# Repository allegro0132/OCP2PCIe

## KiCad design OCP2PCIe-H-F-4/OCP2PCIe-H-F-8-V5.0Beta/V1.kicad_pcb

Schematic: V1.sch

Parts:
C1: C; CP_Elec_6.3x5.4
C2: C; CP_EIA-7343-31_Kemet-D
C3, C4: C; C_1206_3216Metric
J1: PCIe_x8; BUS_PCIexpress_x8
J2: Conn_02x40_Top_Bottom; OCP_Mezz_V2.0
J3, J4: Conn_01x02; PinHeader_1x02_P2.54mm_Vertical
TP1: TestPoint_2Pole; TestPlot
U1: DM02

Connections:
3V3AUX: J1.B10, J2.7, J2.66
+3V3: J1.A9, J1.A10, J1.B8, J2.10, J2.11, J2.12, J2.13, J2.69, J2.70, J2.71, J2.72
+12V: C1.1, J1.A2, J1.A3, J1.B1, J1.B2, J1.B3, J2.61, J2.62, J2.63, J3.1, TP1.1, U1.4
GND: C1.2, C2.2, C3.2, C4.2, J1.A4, J1.A12, J1.A15, J1.A18, J1.A20, J1.A23, J1.A24, J1.A27, J1.A28, J1.A31, J1.A34, J1.A37, J1.A38, J1.A41, J1.A42, J1.A45, J1.A46, J1.A49, J1.B4, J1.B7, J1.B13, J1.B16, J1.B18, J1.B21, J1.B22, J1.B25, J1.B26, J1.B29, J1.B32, J1.B35, J1.B36, J1.B39, J1.B40, J1.B43, J1.B44, J1.B47, J1.B49, J2.5, J2.6, J2.8, J2.9, J2.20, J2.21, J2.24, J2.25, J2.28, J2.29, J2.32, J2.33, J2.36, J2.37, J2.40, J2.41, J2.44, J2.45, J2.48, J2.49, J2.52, J2.53, J2.56, J2.57, J2.60, J2.64, J2.65, J2.67, J2.68, J2.73, J2.79, J2.82, J2.83, J2.86, J2.87, J2.90, J2.91, J2.94, J2.95, J2.98, J2.99, J2.102, J2.103, J2.106, J2.107, J2.110, J2.111, J2.114, J2.115, J2.118, J2.119, J3.2, J4.2, U1.2, U1.3
HSI0_N: J1.A17, J2.31
HSI0_P: J1.A16, J2.30
HSI1_N: J1.A22, J2.35
HSI1_P: J1.A21, J2.34
HSI2_N: J1.A26, J2.39
HSI2_P: J1.A25, J2.38
HSI3_N: J1.A30, J2.43
HSI3_P: J1.A29, J2.42
HSI4_N: J1.A36, J2.47
HSI4_P: J1.A35, J2.46
HSI5_N: J1.A40, J2.51
HSI5_P: J1.A39, J2.50
HSI6_N: J1.A44, J2.55
HSI6_P: J1.A43, J2.54
HSI7_N: J1.A48, J2.59
HSI7_P: J1.A47, J2.58
HSO0_N: J1.B15, J2.89
HSO0_P: J1.B14, J2.88
HSO1_N: J1.B20, J2.93
HSO1_P: J1.B19, J2.92
HSO2_N: J1.B24, J2.97
HSO2_P: J1.B23, J2.96
HSO3_N: J1.B28, J2.101
HSO3_P: J1.B27, J2.100
HSO4_N: J1.B34, J2.105
HSO4_P: J1.B33, J2.104
HSO5_N: J1.B38, J2.109
HSO5_P: J1.B37, J2.108
HSO6_N: J1.B42, J2.113
HSO6_P: J1.B41, J2.112
HSO7_N: J1.B46, J2.117
HSO7_P: J1.B45, J2.116
P5V_AUX: C2.1, C3.1, C4.1, J2.2, J2.3, J2.4, J4.1, TP1.2, U1.1
PERST: J1.A11, J2.17
PRSNT1: J1.A1, J2.1
PRSNT2: J1.B48, J2.120
REFCLK+: J1.A13, J2.26, J2.84
REFCLK-: J1.A14, J2.27, J2.85
WAKE: J1.B11, J2.77

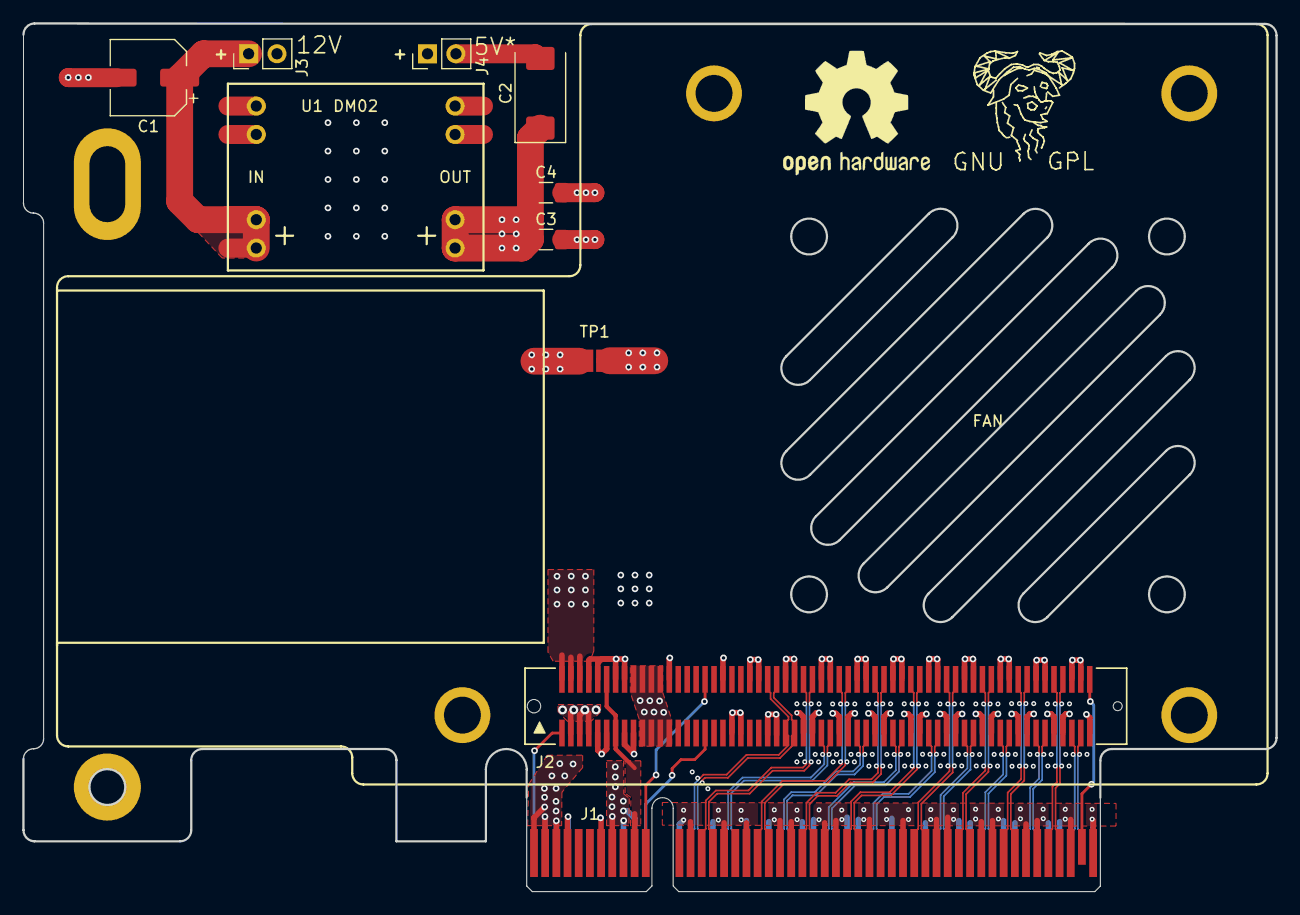
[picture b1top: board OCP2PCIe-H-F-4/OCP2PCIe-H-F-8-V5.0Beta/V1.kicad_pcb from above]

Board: 4 copper layers, 112.1 x 77.6 mm, 11 parts (0 on the bottom side), 43 nets.

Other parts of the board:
FAN: Fan_4010

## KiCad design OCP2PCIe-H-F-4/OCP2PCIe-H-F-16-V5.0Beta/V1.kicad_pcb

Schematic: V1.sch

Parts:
C1, C2, C4, C5: 1uf; C_0402_1005Metric_Pad0.74x0.62mm_HandSolder
C3, C6: 10uf; C_0603_1608Metric_Pad1.08x0.95mm_HandSolder
C7: C; CP_Elec_6.3x5.4
C8: C; CP_EIA-7343-31_Kemet-D
C9, C10: C; C_1206_3216Metric
J1: PCIe_x16; BUS_PCIexpress_x16
J2, J3: Conn_02x40_Top_Bottom; OCP_Mezz_V2.0
J4, J5: Conn_01x02; PinHeader_1x02_P2.54mm_Vertical
L1, L2: L; L_0603_1608Metric_Pad1.05x0.95mm_HandSolder
R2, R6: 34.46; R_0402_1005Metric_Pad0.72x0.64mm_HandSolder
R3, R4, R5, R7, R8, R9: R; R_0402_1005Metric_Pad0.72x0.64mm_HandSolder
TP1: TestPoint_2Pole; TestPlot
U1: DM02
U2: 9DBL411B; SOP65P640X120-20N

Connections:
3V3AUX: J1.B10, J2.7, J2.66, J3.7, J3.66
3V3_A: C1.1, C2.1, C3.1, L1.1, U2.4
3V3_D: C4.1, C5.1, C6.1, L2.1, U2.9, U2.18
+3V3: J1.A9, J1.A10, J1.B8, J2.10, J2.11, J2.12, J2.13, J2.69, J2.70, J2.71, J2.72, J3.10, J3.11, J3.12, J3.13, J3.69, J3.70, J3.71, J3.72, L1.2, L2.2
+12V: C7.1, J1.A2, J1.A3, J1.B1, J1.B2, J1.B3, J2.61, J2.62, J2.63, J3.61, J3.62, J3.63, J4.1, TP1.1, U1.4
DIF0_N: R2.2, U2.20
DIF0_P: R3.2, U2.19
DIF1_N: R4.2, U2.15
DIF1_P: R5.2, U2.14
DIF2_N: R6.2, U2.8
DIF2_P: R7.2, U2.7
DIF3_N: R8.2, U2.12
DIF3_P: R9.2, U2.11
GND: C1.2, C2.2, C3.2, C4.2, C5.2, C6.2, C7.2, C8.2, C9.2, C10.2, J1.A4, J1.A12, J1.A15, J1.A18, J1.A20, J1.A23, J1.A24, J1.A27, J1.A28, J1.A31, J1.A34, J1.A37, J1.A38, J1.A41, J1.A42, J1.A45, J1.A46, J1.A49, J1.A50, J1.A51, J1.A54, J1.A55, J1.A58, J1.A59, J1.A62, J1.A63, J1.A66, J1.A67, J1.A70, J1.A71, J1.A74, J1.A75, J1.A78, J1.A79, J1.A82, J1.B4, J1.B7, J1.B13, J1.B16, J1.B18, J1.B21, J1.B22, J1.B25, J1.B26, J1.B29, J1.B32, J1.B35, J1.B36, J1.B39, J1.B40, J1.B43, J1.B44, J1.B47, J1.B49, J1.B52, J1.B53, J1.B56, J1.B57, J1.B60, J1.B61, J1.B64, J1.B65, J1.B68, J1.B69, J1.B72, J1.B73, J1.B76, J1.B77, J1.B80, J1.B82, J2.5, J2.6, J2.8, J2.9, J2.20, J2.21, J2.24, J2.25, J2.28, J2.29, J2.32, J2.33, J2.36, J2.37, J2.40, J2.41, J2.44, J2.45, J2.48, J2.49, J2.52, J2.53, J2.56, J2.57, J2.60, J2.64, J2.65, J2.67, J2.68, J2.73, J2.79, J2.82, J2.83, J2.86, J2.87, J2.90, J2.91, J2.94, J2.95, J2.98, J2.99, J2.102, J2.103, J2.106, J2.107, J2.110, J2.111, J2.114, J2.115, J2.118, J2.119, J3.5, J3.6, J3.8, J3.9, J3.20, J3.21, J3.24, J3.25, J3.28, J3.29, J3.32, J3.33, J3.36, J3.37, J3.40, J3.41, J3.44, J3.45, J3.48, J3.49, J3.52, J3.53, J3.56, J3.57, J3.60, J3.64, J3.65, J3.67, J3.68, J3.73, J3.79, J3.82, J3.83, J3.86, J3.87, J3.90, J3.91, J3.94, J3.95, J3.98, J3.99, J3.102, J3.103, J3.106, J3.107, J3.110, J3.111, J3.114, J3.115, J3.118, J3.119, J4.2, J5.2, U1.2, U1.3, U2.1, U2.5, U2.6, U2.10, U2.13, U2.16, U2.17
HSI0_N: J1.A17, J2.31
HSI0_P: J1.A16, J2.30
HSI1_N: J1.A22, J2.35
HSI1_P: J1.A21, J2.34
HSI2_N: J1.A26, J2.39
HSI2_P: J1.A25, J2.38
HSI3_N: J1.A30, J2.43
HSI3_P: J1.A29, J2.42
HSI4_N: J1.A36, J2.47
HSI4_P: J1.A35, J2.46
HSI5_N: J1.A40, J2.51
HSI5_P: J1.A39, J2.50
HSI6_N: J1.A44, J2.55
HSI6_P: J1.A43, J2.54
HSI7_N: J1.A48, J2.59
HSI7_P: J1.A47, J2.58
HSI8_N: J1.A53, J3.31
HSI8_P: J1.A52, J3.30
HSI9_N: J1.A57, J3.35
HSI9_P: J1.A56, J3.34
HSI10_N: J1.A61, J3.39
HSI10_P: J1.A60, J3.38
HSI11_N: J1.A65, J3.43
HSI11_P: J1.A64, J3.42
HSI12_N: J1.A69, J3.47
HSI12_P: J1.A68, J3.46
HSI13_N: J1.A73, J3.51
HSI13_P: J1.A72, J3.50
HSI14_N: J1.A77, J3.55
HSI14_P: J1.A76, J3.54
HSI15_N: J1.A81, J3.59
HSI15_P: J1.A80, J3.58
HSO0_N: J1.B15, J2.89
HSO0_P: J1.B14, J2.88
HSO1_N: J1.B20, J2.93
HSO1_P: J1.B19, J2.92
HSO2_N: J1.B24, J2.97
HSO2_P: J1.B23, J2.96
HSO3_N: J1.B28, J2.101
HSO3_P: J1.B27, J2.100
HSO4_N: J1.B34, J2.105
HSO4_P: J1.B33, J2.104
HSO5_N: J1.B38, J2.109
HSO5_P: J1.B37, J2.108
HSO6_N: J1.B42, J2.113
HSO6_P: J1.B41, J2.112
HSO7_N: J1.B46, J2.117
HSO7_P: J1.B45, J2.116
HSO8_N: J1.B51, J3.89
HSO8_P: J1.B50, J3.88
HSO9_N: J1.B55, J3.93
HSO9_P: J1.B54, J3.92
HSO10_N: J1.B59, J3.97
HSO10_P: J1.B58, J3.96
HSO11_N: J1.B63, J3.101
HSO11_P: J1.B62, J3.100
HSO12_N: J1.B67, J3.105
HSO12_P: J1.B66, J3.104
HSO13_N: J1.B71, J3.109
HSO13_P: J1.B70, J3.108
HSO14_N: J1.B75, J3.113
HSO14_P: J1.B74, J3.112
HSO15_N: J1.B79, J3.117
HSO15_P: J1.B78, J3.116
P5V_AUX: C8.1, C9.1, C10.1, J2.2, J2.3, J2.4, J3.2, J3.3, J3.4, J5.1, TP1.2, U1.1
PERST: J1.A11, J2.17, J3.17
PRSNT1: J1.A1, J2.1, J3.1
PRSNT2A: J1.B48, J2.120
PRSNT2B: J1.B81, J3.120
REFCLK0+: J2.84, R3.1
REFCLK0-: J2.85, R2.1
REFCLK1+: J2.26, R5.1
REFCLK1-: J2.27, R4.1
REFCLK2+: J3.84, R7.1
REFCLK2-: J3.85, R6.1
REFCLK3+: J3.26, R9.1
REFCLK3-: J3.27, R8.1
REFCLK+: J1.A13, U2.2
REFCLK-: J1.A14, U2.3
WAKE: J1.B11, J2.77, J3.77

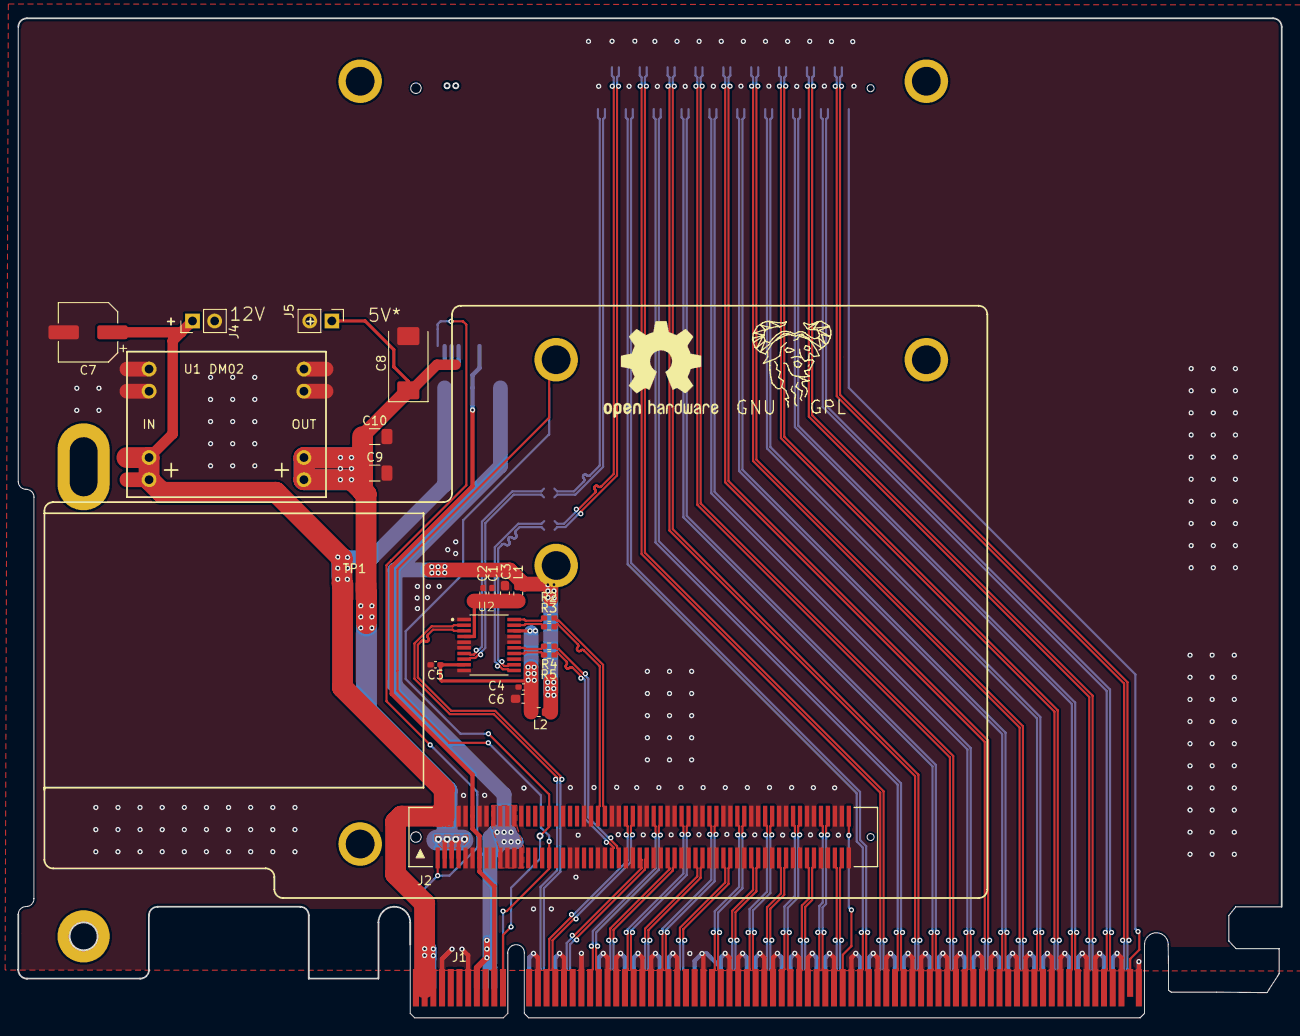
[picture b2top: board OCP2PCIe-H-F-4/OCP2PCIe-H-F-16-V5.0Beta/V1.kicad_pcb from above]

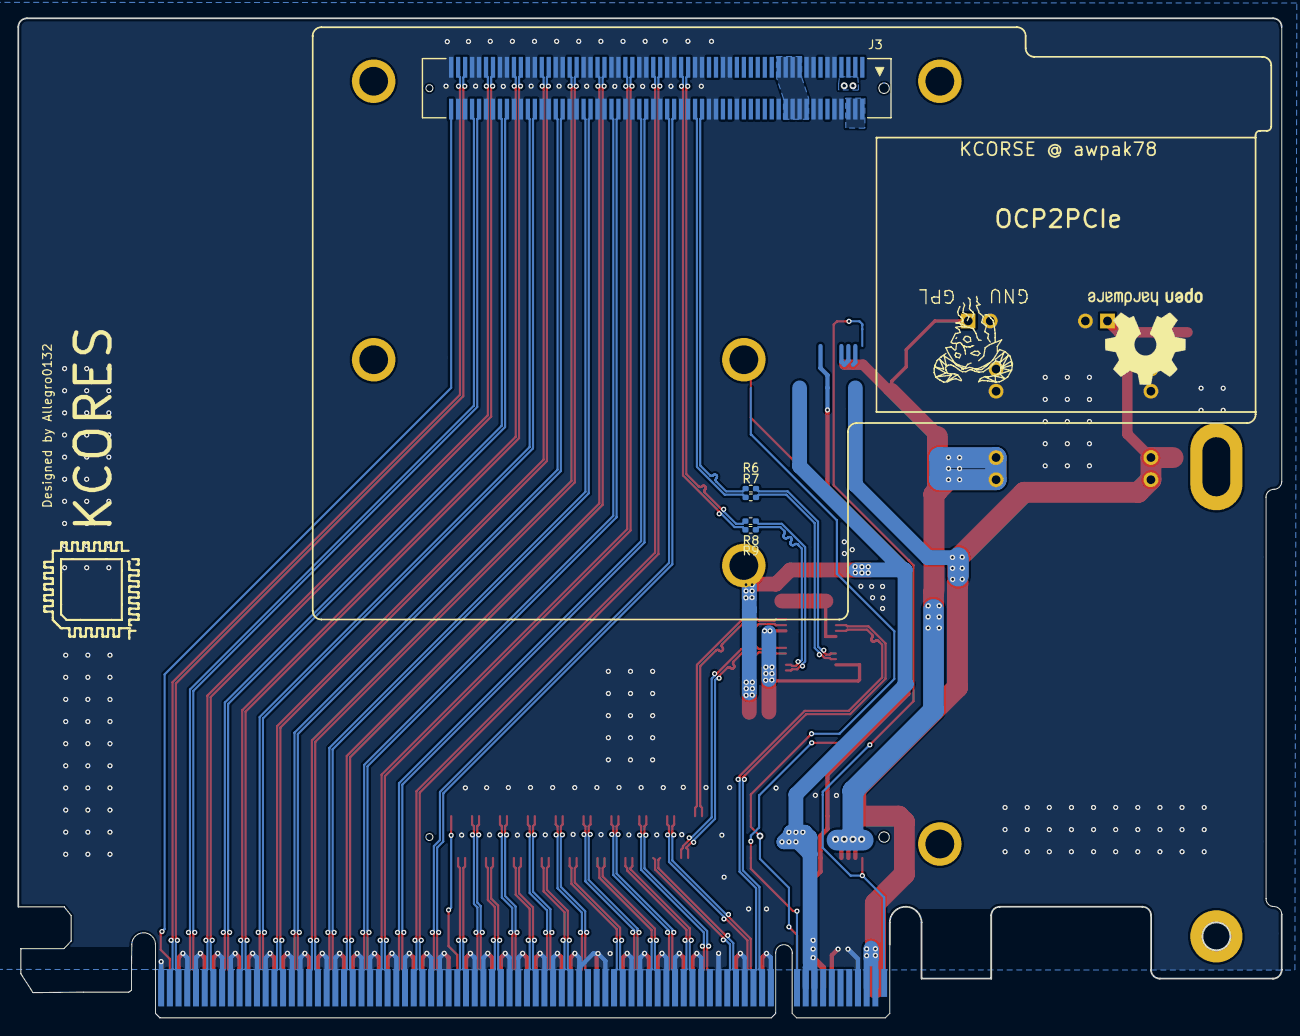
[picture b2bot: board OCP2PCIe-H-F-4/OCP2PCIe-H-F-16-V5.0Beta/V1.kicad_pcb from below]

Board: 2 copper layers, 145.1 x 114.8 mm, 28 parts (5 on the bottom side), 94 nets.

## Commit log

2021-05-23 add clock fanout
2021-05-23 fixed
2021-05-24 tuning pcie lane
2021-06-05 tuning clock
2021-06-05 tuning pcie
2021-06-11 v4.0
    Pciex16
2021-06-12 full
2021-06-24 designed for cx3_vga
2021-07-05 ast2300 first
2021-07-12 四层pcb设计
